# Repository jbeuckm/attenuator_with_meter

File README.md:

attenuator_with_meter
=====================

Output module for a modular synthesizer. This active attenuator steps down from the ~10Vpp modular level to ~5Vpp for line level input to a mixer. An LM3915 is used to display a 10-segment level meter.

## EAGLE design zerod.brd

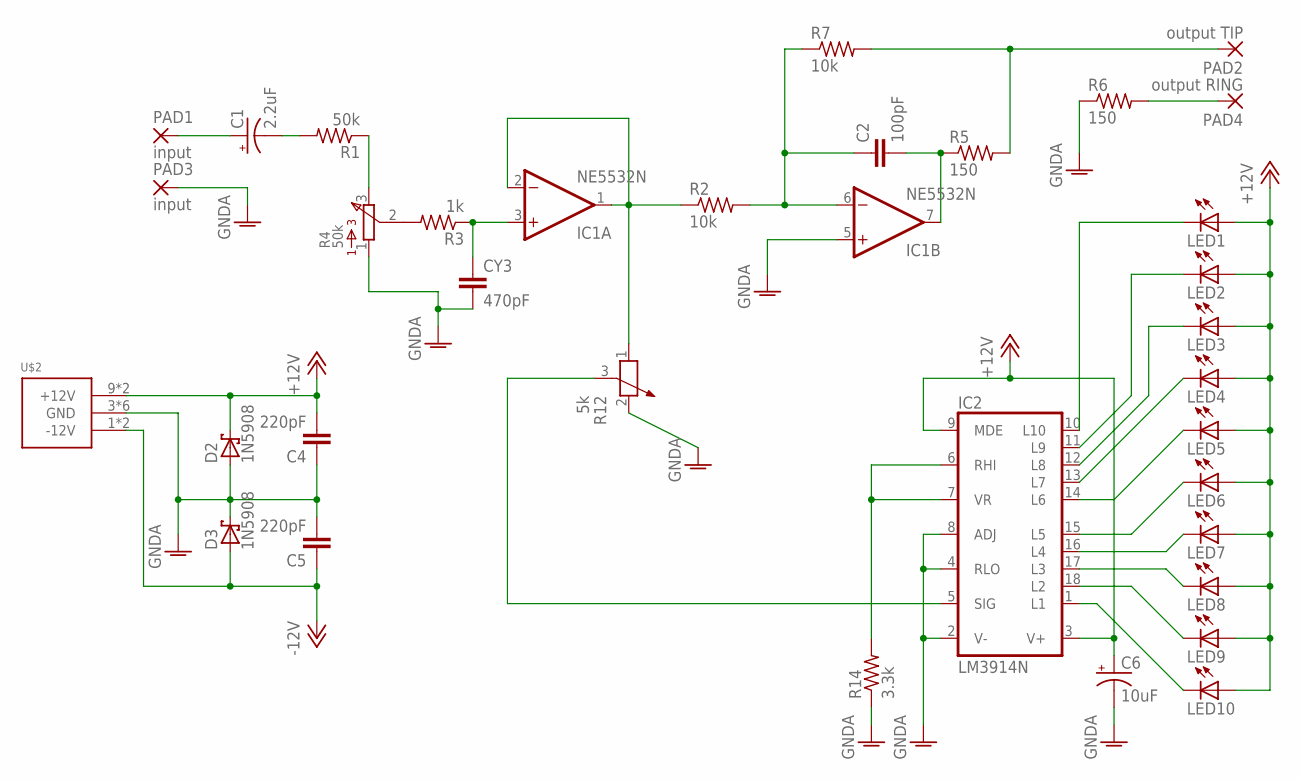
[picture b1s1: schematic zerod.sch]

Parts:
C1: 2.2uF; E15-6
C2: 100pF; C2.5-6
C4, C5: 220pF; C025-024X044
C6: 10uF; E1,8-4
CY3: 470pF; YC7B5
D2, D3: 1N5908; C4111-15
IC1: NE5532N; DIL08
IC2: LM3914N; DIL18
LED1, LED2, LED3, LED4, LED5, LED6, LED7, LED8, LED9, LED10: LED5MM
PAD1, PAD3: input; 3,17/1,3
PAD2: output TIP; 3,17/1,3
PAD4: output RING; 3,17/1,3
R1: 50k; 0207/10
R2, R7: 10k; 0207/10
R3: 1k; 0207/10
R4: 50k; 91
R5, R6: 150; 0207/10
R12: 5k; PT-10S
R14: 3.3k; 0207/10
U$2: POWER_SIMPLE10; POWER_10

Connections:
+12V: C4.2, C6.+, D2.C, IC1.8 (V+), IC2.3 (V+), IC2.9 (MDE), LED1.A, LED2.A, LED3.A, LED4.A, LED5.A, LED6.A, LED7.A, LED8.A, LED9.A, LED10.A, U$2.9 (+12V), U$2.10 (+12V)
-12V: C5.1, D3.A, IC1.4 (V-), U$2.1 (-12V), U$2.2 (-12V)
GNDA: C4.1, C5.2, C6.-, CY3.2, D2.A, D3.C, IC1.5 (+IN), IC2.2 (V-), IC2.4 (RLO), IC2.8 (ADJ), PAD3.1, R4.1, R6.1, R12.2, R14.1, U$2.3 (GND), U$2.4 (GND), U$2.5 (GND), U$2.6 (GND), U$2.7 (GND), U$2.8 (GND)
unnamed: C1.+, PAD1.1
unnamed: C1.-, R1.2
unnamed: R1.1, R4.3
unnamed: PAD4.1, R6.2
unnamed: CY3.1, IC1.3 (+IN), R3.1
unnamed: R3.2, R4.2
unnamed: C2.1, IC1.6 (-IN), R2.2, R7.1
unnamed: C2.2, IC1.7 (OUT), R5.1
unnamed: IC1.1 (OUT), IC1.2 (-IN), R2.1, R12.1
unnamed: IC2.10 (L10), LED1.K (C)
unnamed: IC2.5 (SIG), R12.3
unnamed: IC2.11 (L9), LED2.K (C)
unnamed: IC2.6 (RHI), IC2.7 (VR), R14.2
unnamed: PAD2.1, R5.2, R7.2
unnamed: IC2.12 (L8), LED3.K (C)
unnamed: IC2.13 (L7), LED4.K (C)
unnamed: IC2.14 (L6), LED5.K (C)
unnamed: IC2.15 (L5), LED6.K (C)
unnamed: IC2.16 (L4), LED7.K (C)
unnamed: IC2.17 (L3), LED8.K (C)
unnamed: IC2.18 (L2), LED9.K (C)
unnamed: IC2.1 (L1), LED10.K (C)

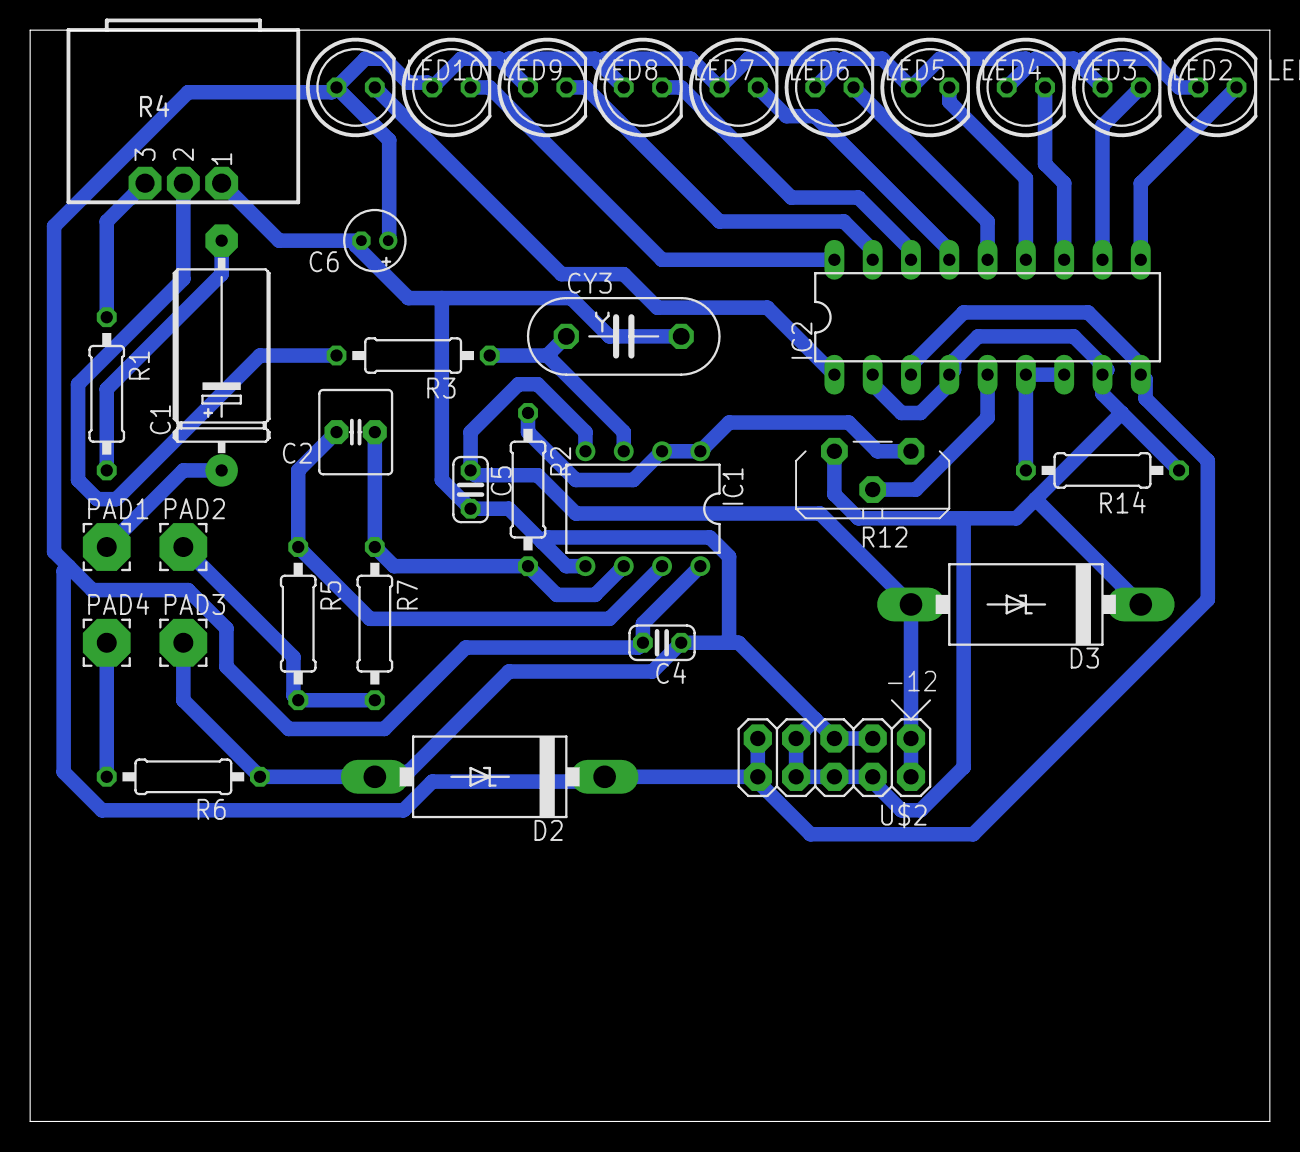
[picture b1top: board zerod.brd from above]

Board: 2 copper layers, 82.2 x 72.4 mm, 34 parts (0 on the bottom side), 25 nets.

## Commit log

2014-10-17 routed board to match updated schematic
2014-10-19 tweaked bit depth for cnc
2014-10-19 set up etch from calculator values
2014-10-19 redid layout
2014-10-20 redid layout for 100%
2014-10-23 rules from atmega min circuit
2014-10-23 rerouted with new rules and gcode with new settings
2014-10-23 ostensibly working board has been cut
2014-10-24 new, smaller board
2014-10-25 cnc front panel for the attenuator
2014-11-10 thicker traces
2014-11-11 trimmer before peak detector
2014-11-12 ditching the peak finder circuit
2014-11-13 no peak finder and balanced
2014-11-13 value set for output filter cap
2014-11-15 regen gcode with new schema
2014-11-17 gcode for balanced version
2014-11-24 readme
